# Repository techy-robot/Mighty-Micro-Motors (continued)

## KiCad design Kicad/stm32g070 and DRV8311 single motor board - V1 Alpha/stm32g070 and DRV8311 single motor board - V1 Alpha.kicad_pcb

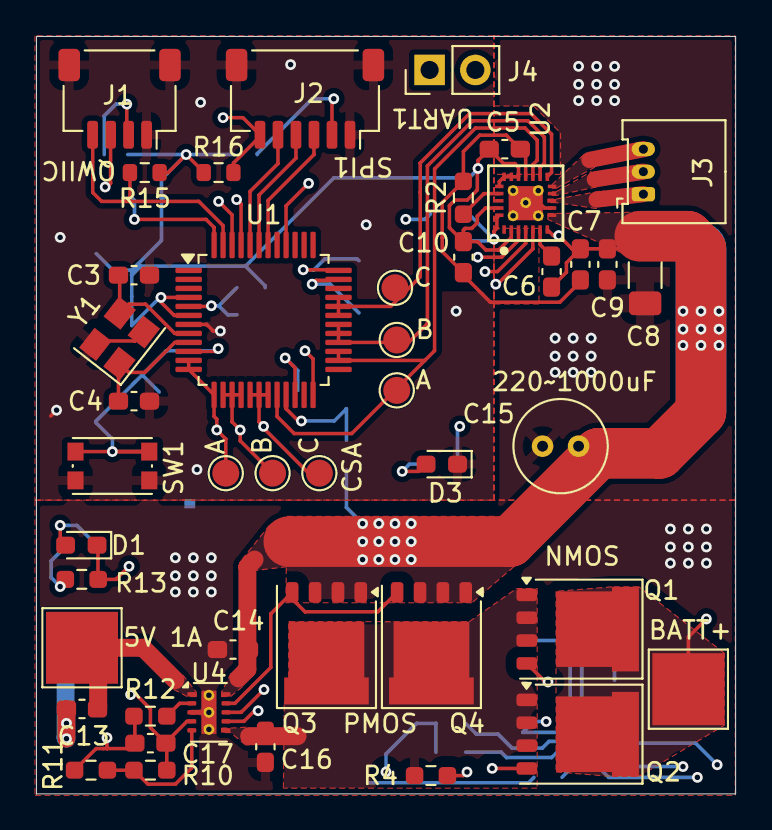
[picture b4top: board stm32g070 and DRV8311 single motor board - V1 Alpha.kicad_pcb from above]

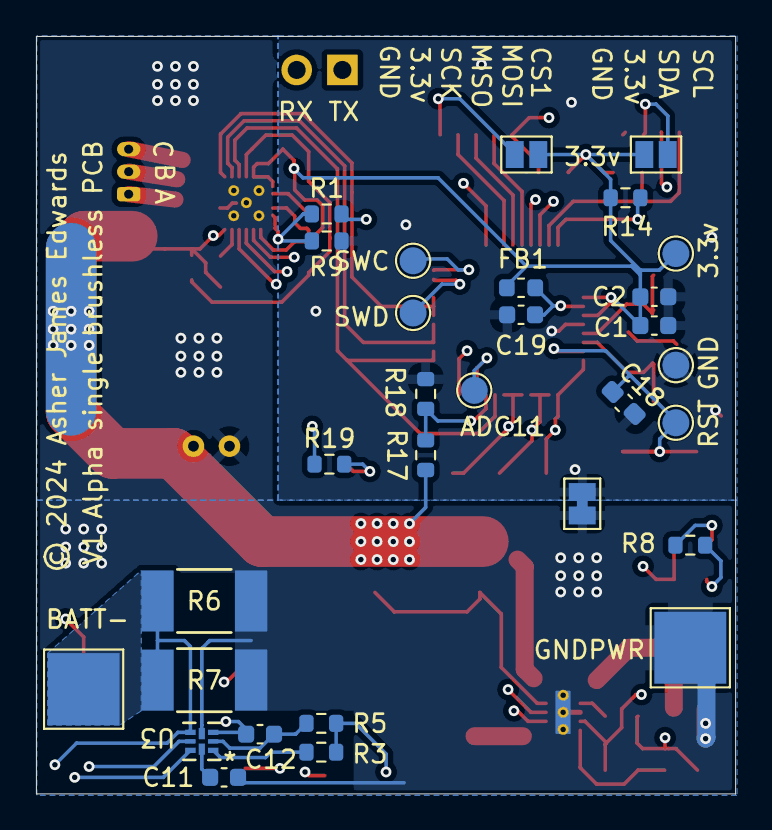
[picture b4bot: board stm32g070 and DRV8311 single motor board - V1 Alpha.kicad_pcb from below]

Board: 4 copper layers, 38.8 x 42.1 mm, 74 parts (30 on the bottom side), 51 nets.

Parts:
C1, C19: 0.1uF; C_0603_1608Metric
C2: 4.7uF; C_0603_1608Metric
C3, C4: 12pF; C_0603_1608Metric_Pad1.08x0.95mm_HandSolder
C5: 4.7uF; C_0603_1608Metric_Pad1.08x0.95mm_HandSolder
C6, C7, C9: 0.1uF, 16v; C_0603_1608Metric_Pad1.08x0.95mm_HandSolder
C8: 220uF, 16 v; C_1206_3216Metric_Pad1.33x1.80mm_HandSolder
C10, C18: 0.1uF; C_0603_1608Metric_Pad1.08x0.95mm_HandSolder
C11: 8nF; C_0603_1608Metric
C12: 1uF, 16v; C_0603_1608Metric
C13, C14, C16: 10uF, 16v; C_0603_1608Metric_Pad1.08x0.95mm_HandSolder
C15: 1000uF, 16v; C_Radial_D5.0mm_H5.0mm_P2.00mm
C17: 1uF; C_0603_1608Metric_Pad1.08x0.95mm_HandSolder
D1, D3: Osram LT Q99G.01 green led; LED_0603_1608Metric_Pad1.05x0.95mm_HandSolder
FB1: 120ohm imp @100mhz; L_0603_1608Metric
H1, H2, H3, H4: 4mm_Pad; TestPoint_Pad_4.0x4.0mm
J1: JST SH SM04B; JST_SH_SM04B-SRSS-TB_1x04-1MP_P1.00mm_Horizontal
J2: JST SH SM06B; JST_SH_SM06B-SRSS-TB_1x06-1MP_P1.00mm_Horizontal
J3: Molex_PicoBlade_53048-0310 Horizontal 3P; Molex_PicoBlade_53048-0310_1x03_P1.25mm_Horizontal
J4: Conn_01x02_Pin; PinHeader_1x02_P2.54mm_Vertical
JP1, JP2: VCC; SolderJumper-2_P1.3mm_Bridged_Pad1.0x1.5mm
L1: GND joiner; SolderJumper-2_P1.3mm_Bridged_Pad1.0x1.5mm
Q1: NMOS, sir404dp; PQFN-8-EP_6x5mm_P1.27mm_Generic
Q2: NMOS; PQFN-8-EP_6x5mm_P1.27mm_Generic
Q3: PMOS,Si7157DP; PQFN-8-EP_6x5mm_P1.27mm_Generic
Q4: PMOS; PQFN-8-EP_6x5mm_P1.27mm_Generic
R1, R17: 100k; R_0603_1608Metric
R2: 47k; R_0603_1608Metric_Pad0.98x0.95mm_HandSolder
R3: 20ohm; R_0603_1608Metric
R4, R13: 2k; R_0603_1608Metric_Pad0.98x0.95mm_HandSolder
R5: 300ohm; R_0603_1608Metric
R6: Same, 1000uOhm; RES_WSLF2512_VIS-M
R7: Vishay WSLF2512, 1%, 300uOhm; RES_WSLF2512_VIS-M
R8: 402 ohm; R_0603_1608Metric
R9, R18: 150k; R_0603_1608Metric
R10, R12: 1k; R_0603_1608Metric_Pad0.98x0.95mm_HandSolder
R11: 230ohm; R_0603_1608Metric_Pad0.98x0.95mm_HandSolder
R14, R15, R16: 10k; R_0603_1608Metric
R19: 80.6 ohm; R_0603_1608Metric
SW1: SW_Push; SW_Push_1P1T_NO_CK_KMR2
TP1, TP2, TP3, TP4, TP5, TP6: TestPoint; TestPoint_Pad_D1.5mm
TP7, TP8, TP9, TP10, TP11, TP12: TestPoint_Pad_D1.5mm
U1: STM32G070CBTr; LQFP-48_7x7mm_P0.5mm
U2: DRV8311HRRWR; DRV8311_0.3mmVias
U3: BQ298012RUGT; RUG8_TEX
U4: BQ25060; WSON-10-1EP_2x3mm_P0.5mm_EP0.84x2.4mm_ThermalVias_0.3mm
Y1: ABM8-16.000MHZ-10-1-U-T; Crystal_SMD_Abracon_ABM8G-4Pin_3.2x2.5mm

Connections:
/1A: TP7.1, U1.20 (PB1), U1.26 (PB14), U1.27 (PB15), U2.15 (INHA)
/1B: TP8.1, U1.28 (PA8), U1.29 (PA9/NC), U1.30 (PC6), U2.14 (INHB)
/1C: TP9.1, U1.31 (PC7), U1.32 (PA10/NC), U1.33 (PA11/PA9), U2.13 (INHC)
/1CSA-A: TP10.1, U1.11 (PA0), U1.12 (PA1), U1.13 (PA2), U2.5 (SOA)
/1CSA-B: TP11.1, U1.14 (PA3), U1.15 (PA4), U1.16 (PA5), U2.4 (SOB)
/1CSA-C: TP12.1, U1.17 (PA6), U1.18 (PA7), U1.19 (PB0), U2.3 (SOC)
/ADC10/VBATT: R17.1, R18.2, U1.21 (PB2)
/ADC11: TP6.1, U1.22 (PB10)
/CS1: J2.6, R16.2, U1.40 (PD2)
/LED: R19.1, U1.24 (PB12)
/MISO1: J2.4, U1.43 (PB4)
/MOSI1: J2.5, U1.44 (PB5)
/MOTORPWR: C6.2, C7.1, C8.1, C9.1, C14.1, C15.1, Q3.1 (S), Q3.2 (S), Q3.3 (S), Q4.1 (S), Q4.2 (S), Q4.3 (S), R1.2, R17.2, U2.7 (VIN_AVDD), U2.8 (VM), U4.10 (OUT)
/NRST: C18.1, SW1.2, TP1.1, U1.10 (NRST)
/PSU/BATT+: H1.1, Q1.5 (D), Q2.5 (D), R3.1, R5.1
/PSU/BATT-: C12.2, H2.1, R6.1, R7.1, U3.3 (VSS), U3.5 (CTR)
/PSU/IN: C13.1, H3.1, U4.1 (IN)
/PSU/LDO 4.9v: C17.2, R8.1, R10.1, R13.2, U4.4 (LDO)
/PSU/Pack+: C16.2, Q1.1 (S), Q1.2 (S), Q1.3 (S), Q2.1 (S), Q2.2 (S), Q2.3 (S), Q3.5 (D), Q4.5 (D), R4.1, U4.6 (BAT)
/PSU/~CHG: D1.1 (K), R13.1, U4.8 (~CHG)
/SCK1: J2.3, U1.42 (PB3)
/SCL1: J1.4, R15.2, U1.47 (PB8)
/SDA1: J1.3, R14.2, U1.48 (PB9)
/SWC: TP3.1, U1.36 (PA14)
/SWD: TP2.1, U1.35 (PA13)
/USART1_RX: J4.2, U1.46 (PB7)
/USART1_TX: J4.1, U1.45 (PB6)
GND: C1.2, C2.2, C3.2, C4.2, C5.1, C7.2, C10.1, C17.1, C18.2, C19.1, D3.1 (K), J1.1, J1.MP (MountPin), J2.1, J2.MP (MountPin), L1.1, R2.1, R9.1, R11.2, R12.1, R18.1, SW1.1, TP5.1, U1.7 (VSS), U2.16 (AGND), U4.7 (EN), Y1.2, Y1.4
GNDPWR: C8.2, C9.2, C11.2, C13.2, C14.2, C15.2, C16.1, H4.1, L1.2, R6.2, R7.2, U2.9 (PGND), U2.25 (PowerPAD), U3.4 (CS), U4.3 (VSS), U4.11 (VSS)
unnamed: D1.2 (A), R8.2
unnamed: D3.2 (A), R19.2
unnamed: J1.2, JP1.2 (B)
unnamed: J2.2, JP2.2 (B)
unnamed: J3.1, U2.10 (OUTA)
unnamed: J3.2, U2.11 (OUTB)
unnamed: J3.3, U2.12 (OUTC)
unnamed: Q1.4 (G), Q2.4 (G), U3.7 (DSG)
unnamed: Q3.4 (G), Q4.4 (G), U4.9 (BGATE)
unnamed: C3.1, U1.8 (PF0), Y1.3
unnamed: C4.1, U1.9 (PF1), Y1.1
unnamed: C19.2, FB1.1, U1.5 (VREF+)
unnamed: C6.1, U2.6 (CP)
unnamed: R2.2, U2.21 (GAIN)
unnamed: R1.1, R9.2, U2.24 (SLEEP_N)
unnamed: R3.2, U3.1 (BAT)
unnamed: C11.1, U3.8 (CHG)
unnamed: R4.2, U3.6 (PACK)
unnamed: C12.1, R5.2, U3.2 (VDD)
unnamed: R12.2, U4.2 (ISET)
unnamed: R10.2, R11.1, U4.5 (TS)
VDD: C1.1, C2.1, C5.2, C10.2, FB1.2, JP1.1 (A), JP2.1 (A), R14.1, R15.1, R16.1, TP4.1, U1.4 (VBAT), U1.6 (VDD), U2.2 (CSAREF), U2.17 (AVDD), U2.18 (INLA), U2.19 (INLB), U2.20 (INLC), U2.23 (MODE)

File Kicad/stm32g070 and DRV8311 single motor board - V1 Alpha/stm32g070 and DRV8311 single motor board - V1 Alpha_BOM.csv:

"Reference","Value","Datasheet","Footprint","Qty","DNP"
"C1,C10,C18,C19","0.1uF","~","-- mixed values --","4",""
"C2,C5","4.7uF","~","-- mixed values --","2",""
"C3,C4","12pF","~","Capacitor_SMD:C_0603_1608Metric_Pad1.08x0.95mm_HandSolder","2",""
"C6,C7,C9","0.1uF, 16v","~","Capacitor_SMD:C_0603_1608Metric_Pad1.08x0.95mm_HandSolder","3",""
"C11","8nF","~","Capacitor_SMD:C_0603_1608Metric","1",""
"C12","1uF, 16v","~","Capacitor_SMD:C_0603_1608Metric","1",""
"C13,C14,C16","10uF, 16v","~","Capacitor_SMD:C_0603_1608Metric_Pad1.08x0.95mm_HandSolder","3",""
"C15","1000uF, 16v","~","Capacitor_THT:C_Radial_D5.0mm_H5.0mm_P2.00mm","1",""
"C17","1uF","~","Capacitor_SMD:C_0603_1608Metric_Pad1.08x0.95mm_HandSolder","1",""
"D1,D3","Osram LT Q99G.01 green led","~","LED_SMD:LED_0603_1608Metric_Pad1.05x0.95mm_HandSolder","2",""
"FB1","120ohm imp @100mhz","~","Inductor_SMD:L_0603_1608Metric","1",""
"J1","JST SH SM04B","~","Connector_JST:JST_SH_SM04B-SRSS-TB_1x04-1MP_P1.00mm_Horizontal","1",""
"J2","JST SH SM06B","~","Connector_JST:JST_SH_SM06B-SRSS-TB_1x06-1MP_P1.00mm_Horizontal","1",""
"J3","Molex_PicoBlade_53048-0310 Horizontal 3P","~","Connector_Molex:Molex_PicoBlade_53048-0310_1x03_P1.25mm_Horizontal","1",""
"J4","Conn_01x02_Pin","~","Connector_PinHeader_2.54mm:PinHeader_1x02_P2.54mm_Vertical","1",""
"L1","GND joiner","~","Jumper:SolderJumper-2_P1.3mm_Bridged_Pad1.0x1.5mm","1",""
"Q1","NMOS, sir404dp","https://ngspice.sourceforge.io/docs/ngspice-html-manual/manu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","Package_DFN_QFN:PQFN-8-EP_6x5mm_P1.27mm_Generic","1",""
"Q2","NMOS","https://ngspice.sourceforge.io/docs/ngspice-html-manual/manu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","Package_DFN_QFN:PQFN-8-EP_6x5mm_P1.27mm_Generic","1",""
"Q3","PMOS,Si7157DP","https://ngspice.sourceforge.io/docs/ngspice-html-manual/manu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","Package_DFN_QFN:PQFN-8-EP_6x5mm_P1.27mm_Generic","1",""
"Q4","PMOS","https://ngspice.sourceforge.io/docs/ngspice-html-manual/manu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","Package_DFN_QFN:PQFN-8-EP_6x5mm_P1.27mm_Generic","1",""
"R1,R17","100k","~","Resistor_SMD:R_0603_1608Metric","2",""
"R2","47k","~","Resistor_SMD:R_0603_1608Metric_Pad0.98x0.95mm_HandSolder","1",""
"R3","20ohm","~","Resistor_SMD:R_0603_1608Metric","1",""
"R4,R13","2k","~","Resistor_SMD:R_0603_1608Metric_Pad0.98x0.95mm_HandSolder","2",""
"R5","300ohm","~","Resistor_SMD:R_0603_1608Metric","1",""
"R6","Same, 1000uOhm","~","vishay_wslf:RES_WSLF2512_VIS-M","1",""
"R7","Vishay WSLF2512, 1%, 300uOhm","~","vishay_wslf:RES_WSLF2512_VIS-M","1",""
"R8","402 ohm","~","Resistor_SMD:R_0603_1608Metric","1",""
"R9,R18","150k","~","Resistor_SMD:R_0603_1608Metric","2",""
"R10,R12","1k","~","Resistor_SMD:R_0603_1608Metric_Pad0.98x0.95mm_HandSolder","2",""
"R11","230ohm","~","Resistor_SMD:R_0603_1608Metric_Pad0.98x0.95mm_HandSolder","1",""
"R14,R15,R16","10k","~","Resistor_SMD:R_0603_1608Metric","3",""
"R19","80.6 ohm","~","Resistor_SMD:R_0603_1608Metric","1",""
"SW1","SW_Push","~","Button_Switch_SMD:SW_Push_1P1T_NO_CK_KMR2","1",""
"TP1,TP2,TP3,TP4,TP5,TP6","TestPoint","~","TestPoint:TestPoint_Pad_D1.5mm","6",""
"TP7,TP8,TP9,TP10,TP11,TP12","~","~","TestPoint:TestPoint_Pad_D1.5mm","6",""
"U1","STM32G070CBTr","https://www.st.com/resource/en/datasheet/stm32g070cb.pdf","Package_QFP:LQFP-48_7x7mm_P0.5mm","1",""
"U2","DRV8311HRRWR","https://www.ti.com/lit/ds/symlink/drv8311.pdf","custom_Driver_Motor:DRV8311_0.3mmVias","1",""
"U3","BQ298012RUGT","BQ298000RUGT","bq298rugt:RUG8_TEX","1",""
"U4","BQ25060","https://www.ti.com/lit/ds/symlink/bq25060.pdf","custom_Power:WSON-10-1EP_2x3mm_P0.5mm_EP0.84x2.4mm_ThermalVias_0.3mm","1",""
"Y1","ABM8-16.000MHZ-10-1-U-T","~","Crystal:Crystal_SMD_Abracon_ABM8G-4Pin_3.2x2.5mm","1",""

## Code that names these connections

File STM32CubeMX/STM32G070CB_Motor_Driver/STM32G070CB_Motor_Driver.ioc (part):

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Mcu.Name=STM32G070CBTx
Mcu.Package=LQFP48
Mcu.UserName=STM32G070CBTx
PA0.Mode=IN0
PA0.Signal=ADC1_IN0
PA1.Mode=IN1
PA1.Signal=ADC1_IN1
PA10.Signal=S_TIM1_CH3
PA11\ [PA9].Signal=S_TIM1_CH4
PA12\ [PA10].Mode=I2C
PA12\ [PA10].Signal=I2C2_SDA
PA13.Mode=Serial_Wire
PA13.Signal=SYS_SWDIO
PA14-BOOT0.Mode=Serial_Wire
PA14-BOOT0.Signal=SYS_SWCLK
PA2.Mode=IN2
PA2.Signal=ADC1_IN2
PA3.Mode=IN3
PA3.Signal=ADC1_IN3
PA4.Mode=IN4
PA4.Signal=ADC1_IN4
PA5.Mode=IN5
PA5.Signal=ADC1_IN5
PA6.Mode=IN6
PA6.Signal=ADC1_IN6
PA7.Mode=IN7
PA7.Signal=ADC1_IN7
PA8.Signal=S_TIM1_CH1
PA9.Signal=S_TIM1_CH2
PB0.Mode=IN8
PB0.Signal=ADC1_IN8
PB1.Signal=S_TIM3_CH4
PB10.Mode=IN11
PB10.Signal=ADC1_IN11
PB11.Mode=Full_Duplex_Master
PB11.Signal=SPI2_MOSI
PB13.Mode=I2C
PB13.Signal=I2C2_SCL
PB14.Signal=S_TIM15_CH1
PB15.Signal=S_TIM15_CH2
PB2.Mode=IN10
PB2.Signal=ADC1_IN10
PB3.Mode=Full_Duplex_Master
PB3.Signal=SPI1_SCK
PB4.Mode=Full_Duplex_Master
PB4.Signal=SPI1_MISO
PB5.Mode=Full_Duplex_Master
PB5.Signal=SPI1_MOSI
PB6.Mode=Asynchronous
PB6.Signal=USART1_TX
PB7.Mode=Asynchronous
PB7.Signal=USART1_RX
PB8.Mode=I2C
PB8.Signal=I2C1_SCL
PB9.Mode=I2C
PB9.Signal=I2C1_SDA
PC6.Signal=S_TIM3_CH1
PC7.Signal=S_TIM3_CH2
PD1.Mode=Full_Duplex_Master
PD1.Signal=SPI2_SCK
PD3.Mode=Full_Duplex_Master
PD3.Signal=SPI2_MISO
PF0-OSC_IN\ (PF0).Mode=HSE-External-Oscillator
PF0-OSC_IN\ (PF0).Signal=RCC_OSC_IN
PF1-OSC_OUT\ (PF1).Mode=HSE-External-Oscillator
PF1-OSC_OUT\ (PF1).Signal=RCC_OSC_OUT
RCC.HSE_VALUE=16000000
RCC.SYSCLKFreq_VALUE=64000000
RCC.SYSCLKSource=RCC_SYSCLKSOURCE_PLLCLK
board=custom

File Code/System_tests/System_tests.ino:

/*
  Created by Asher Edwards
  Last updated Jul 16, 2024
*/

#include <hal_conf_extra.h> 
#include <SPI.h>

// Clock settings, the only thing changed from default was the clock source for external
extern "C" void SystemClock_Config(void)
{
  RCC_OscInitTypeDef RCC_OscInitStruct = {};
  RCC_ClkInitTypeDef RCC_ClkInitStruct = {};

  /** Configure the main internal regulator output voltage
  */
  HAL_PWREx_ControlVoltageScaling(PWR_REGULATOR_VOLTAGE_SCALE1);
  /** Initializes the RCC Oscillators according to the specified parameters
  * in the RCC_OscInitTypeDef structure. Here I have enabled the external clcok as the source
  */
  RCC_OscInitStruct.OscillatorType = RCC_OSCILLATORTYPE_HSE;
  RCC_OscInitStruct.HSEState = RCC_HSE_ON;
  RCC_OscInitStruct.PLL.PLLState = RCC_PLL_ON;
  RCC_OscInitStruct.PLL.PLLSource = RCC_PLLSOURCE_HSE;
  RCC_OscInitStruct.PLL.PLLM = RCC_PLLM_DIV1;
  RCC_OscInitStruct.PLL.PLLN = 8;
  RCC_OscInitStruct.PLL.PLLP = RCC_PLLP_DIV2;
  RCC_OscInitStruct.PLL.PLLR = RCC_PLLR_DIV2;
  if (HAL_RCC_OscConfig(&RCC_OscInitStruct) != HAL_OK) {
    Error_Handler();
  }
  /** Initializes the CPU, AHB and APB buses clocks
  */
  RCC_ClkInitStruct.ClockType = RCC_CLOCKTYPE_HCLK | RCC_CLOCKTYPE_SYSCLK
                                | RCC_CLOCKTYPE_PCLK1;
  RCC_ClkInitStruct.SYSCLKSource = RCC_SYSCLKSOURCE_PLLCLK;
  RCC_ClkInitStruct.AHBCLKDivider = RCC_SYSCLK_DIV1;
  RCC_ClkInitStruct.APB1CLKDivider = RCC_HCLK_DIV1;

  if (HAL_RCC_ClockConfig(&RCC_ClkInitStruct, FLASH_LATENCY_2) != HAL_OK) {
    Error_Handler();
  }
}

//-----------------Pins-------------------

#define LED PB12

#define CSA_A PA0 //PA0 - 2
#define CSA_B PA3 //PA3 - 5
#define CSA_C PA6 //PA6,PA7,PB0

#define OUT_A PB1 //PB1, PB14, PB14
#define OUT_B PA8 //PA8, PA9, PC6
#define OUT_C PA6 //PC7, PA10, PA11

#define CS1 PD2 //for the first SPI bus

//Found in the datasheet. This is in mV
#define VREFINT 1212
#define ADC_RANGE 4096

//-------------------Interfaces-------------------------
//                      RX    TX
HardwareSerial Serial1(PB7, PB6);

//         MOSI  MISO  SCLK  SSEL
SPIClass SPI_1(PB5, PB4, PB3);

const byte READ = 0b01000000;     // MA735 read command
const byte WRITE = 0b10000000;   // MA735's write command

// the setup function runs once when you press reset or power the board
void setup() {
  // initialize digital pin PB12 as an output. This is the LED pin on my stm32 based motor control board
  pinMode(LED, OUTPUT);

  pinMode(CS1, OUTPUT);
  SPI_1.begin();

  pinMode(CSA_A, INPUT);
  pinMode(CSA_B, INPUT);
  pinMode(CSA_C, INPUT);
  analogReadResolution(12);//Max value is 4096, at 3.3v

  Serial1.begin(19200);

  //Blink twice on start
  digitalWrite(LED, HIGH);
  delay(200);
  digitalWrite(LED, LOW);
  delay(200);
  digitalWrite(LED, HIGH);
  delay(200);
  digitalWrite(LED, LOW);
}

// the loop function runs over and over again forever
void loop() {

  int a = analogRead(CSA_A);
  int b = analogRead(CSA_B);
  int c = analogRead(CSA_C);
  float vref = readVref();

  Serial1.print("Clock freq is: ");//check system clock speed
  Serial1.println(F_CPU);
  Serial1.print("CSA Voltages: ");
  Serial1.print(String(readVoltage(vref, CSA_A)) + ", ");
  Serial1.print(String(readVoltage(vref, CSA_B)) + ", ");
  Serial1.println(String(readVoltage(vref, CSA_C)));
  Serial1.println("Vref(mV):" + String(vref));
  Serial1.println("Vbat(V):" + String(readVoltage(vref, AVBAT)));
  Serial1.println("Temperature(°C):" + String(readTempSensor(vref)));
  Serial1.println("Sensor Data: " + String(readSensor()));
  delay(2000);
}

//alternative analog to voltage, but accounting for voltage reference
static float readVoltage(int32_t VRef, uint32_t pin) {
  return (__LL_ADC_CALC_DATA_TO_VOLTAGE(VRef, analogRead(pin), LL_ADC_RESOLUTION_12B))/1000.0;
}


static int32_t readVref() {
  return (VREFINT * ADC_RANGE / analogRead(AVREF)); // ADC sample to mV
}

static int32_t readTempSensor(int32_t VRef) {
  return (__LL_ADC_CALC_TEMPERATURE(VRef, analogRead(ATEMP), LL_ADC_RESOLUTION_12B));
}

//Read the sensor data
unsigned int readSensor() {
  byte inByte = 0;           // incoming byte from the SPI
  unsigned int result = 0;   // result to return

  // take the chip select low to select the device:
  digitalWrite(CS1, LOW);
  // send a value of 0 to read the bytes
  result = SPI_1.transfer(0x00);//first part
  result = result << 8;
  inByte = SPI_1.transfer(0x00);//second part
  // combine the byte you just got with the previous one:
  result = result | inByte;
  // take the chip select high to de-select:
  digitalWrite(CS1, HIGH);
  // return the result:
  return (result);
}

//Read from a register:
unsigned int readRegister(byte thisRegister, int bytesToRead) {
  byte inByte = 0;           // incoming byte from the SPI
  unsigned int result = 0;   // result to return
  Serial.print(thisRegister, BIN);
  Serial.print("\t");
  // MA735 expects the register name to be in the lower 5 bits
  // of the byte. So shift the bits right by three bits:
  thisRegister = thisRegister >> 3;
  // now combine the address and the command into one byte
  uint16_t dataToSend = READ & thisRegister ; //Read should be 010 in binary
  Serial.println(thisRegister, BIN);
  // take the chip select low to select the device:
  digitalWrite(CS1, LOW);
  // send the device the register you want to read:
  SPI_1.transfer(dataToSend);
  // send a value of 0 to read the first byte returned:
  result = SPI_1.transfer(0x00);
  // decrement the number of bytes left to read:
  bytesToRead--;
  // if you still have another byte to read:
  if (bytesToRead > 0) {
    // shift the first byte left, then get the second byte:
    result = result << 8;
    inByte = SPI_1.transfer(0x00);
    // combine the byte you just got with the previous one:
    result = result | inByte;
    // decrement the number of bytes left to read:
    bytesToRead--;
  }
  // take the chip select high to de-select:
  digitalWrite(CS1, HIGH);
  // return the result:
  return (result);
}

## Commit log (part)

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2024-06-26 Adding current Kicad files
    I previously was not tracking these files on GitHub, so its a rather big commit.
2024-07-05 Filled out README documentation
    Added a description of the project and the individual components.
2024-07-05 Added Progress Log with pictures
2024-07-06 Created Blink example sketch and changed pin number
2024-07-07 Updated progress log, Added Flipper zero programmer support
    Make sure to delete `.config/arduino-ide` to clear up the cache and get the programmer to show up.
2024-07-07 Added correct path for openocd runtime
    In the definition when you have .path, it actually means go one more folder down. That way you don't have to manually type the version number.
2024-07-07 Add pulsing LED heartbeat instead to try out
2024-07-08 Trying out clock settings and serial support
2024-07-16 Fixed Analog read encoding error
2024-07-16 Added internal analog read for temp and for input voltage
2024-07-16 Updated CSA analog reads to use VREF
2024-07-16 Working SPI sensor data read
    The issue was with the default pin definitions. I created an instance with the correct SPI pins.
2024-07-16 Started writing SimpleFOC setup code
2024-07-17 Preliminary MA735 support
    All I did in this was copy the MA730 code and rename everything.
2024-07-17 Added missing registers and cmds
    The two that weren't already implemented was the resolution/speed tradeoff setting (Filter Window), and the ABZ hysteresis setting.
2024-07-17 Fixed switch case typos
    It wasn't compiling last night, because of a few typos. Also switch statements only operate on integers or similar, not strings or floats.
2024-07-17 Added write safety check
    It reads the register before writing. If it is the exact same value, it will not write. This saves time and increases the NVM lifetime, since it has only 1000 cycles!
2024-07-17 Added motor phase resistance, update Log
2024-07-17 Update progress log, compiled code
    I had the wrong names for commander in some places. Code takes up 80kb!
2024-07-18 Some quick fixes
    The motors will spin, however it is only at 100 radians/s and it doesn't like other speeds higher or lower. It whines a lot.
2024-07-18 Back to sinusoidal, changed current sense amount
2024-07-19 Magnetic encoder motor test piece complete
2024-07-19 Skip current sense alignment
    It worked on initialization, however it keeps swapping to the wrong pins. All the current sense align really does is checks and fixes pin errors, but I am pretty sure the pins match up
2024-07-23 Added timing mechanism, absolute sensor position
    I also switched to SpaceVectorPWM because its more efficient, and bumped the current limit back up to 2.5 amps
2024-07-23 Added update time command, and serial usb wait
2024-07-25 Start rework of gearbox base
    I am adding parametric variables in Onshape, and added screw holes that should universally support all my future gearboxes
2024-07-25 Added fan blade on central shaft
    This is a paddle blade like found in power tools and drills. Its not a very efficient fan blade but it works in both directions. Onshape: https://cad.onshape.com/documents/c861ec30af8169cf9c14bd7f/w/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
2024-07-26 Incomplete cycloidal with pass through
    Onshape: https://cad.onshape.com/documents/c861ec30af8169cf9c14bd7f/w/e538486c85e6a5fe77cd1d33/m/884b7a8ee5dcba20016fd244/e/7383c3da91d908f3c2a75881
2024-07-27 Added wire slots in cycloidal
    Onshape: https://cad.onshape.com/documents/c861ec30af8169cf9c14bd7f/w/e538486c85e6a5fe77cd1d33/m/a67cb1fcdf15daad4af4e84a/e/7383c3da91d908f3c2a75881
2024-07-27 Shrinking disc size
    Currently it looks like the smallest I can feasible go is 16mm. I have the number of teeth set to be divisible by 3, so the 3 axle bearings can nestle into the patter of the teeth. I also started wor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
    Onshape: https://cad.onshape.com/documents/c861ec30af8169cf9c14bd7f/w/e538486c85e6a5fe77cd1d33/m/ab9855c3639a3ccbf2450367/e/7383c3da91d908f3c2a75881
2024-07-28 Can't figure out eccentric screw and wire holes
    Onshape: https://cad.onshape.com/documents/c861ec30af8169cf9c14bd7f/w/e538486c85e6a5fe77cd1d33/m/1e100a53234ceef647306cbe/e/7383c3da91d908f3c2a75881
2024-07-29 Tolerance adjustments and adding bearing
    I tweaked a lot of the tolerances, and added bearings around all the little rods.
    Onshape: https://cad.onshape.com/documents/c861ec30af8169cf9c14bd7f/w/e538486c85e6a5fe77cd1d33/m/66f398e2432e977fad1e9c49/e/395711bbc38dcc987be1be1a
2024-07-29 Fixed 2nd disc, working on output stage
    Onshape: https://cad.onshape.com/documents/c861ec30af8169cf9c14bd7f/w/e538486c85e6a5fe77cd1d33/m/98de684524afdfbcdc4f0564/e/7383c3da91d908f3c2a75881
2024-07-29 Finished sensor mount
    Unfortunately the magnet needed for encoding is sticking out the top quite a bit. The only way I could fix this is if I remove the sensor from the on axis position and moved it to the side, which wou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
    Onshape: https://cad.onshape.com/documents/c861ec30af8169cf9c14bd7f/w/e538486c85e6a5fe77cd1d33/m/034e83fa55fcec580c0735db/e/7383c3da91d908f3c2a75881
2024-07-29 Still fixing broken references
    Onshape https://cad.onshape.com/documents/c861ec30af8169cf9c14bd7f/w/e538486c85e6a5fe77cd1d33/m/b95fba314a62f127e0e52bbb/e/7383c3da91d908f3c2a75881
2024-07-30 Animated cycloidal
    Note that the changes are only visible in Onshape really
    Onshape: https://cad.onshape.com/documents/c861ec30af8169cf9c14bd7f/w/e538486c85e6a5fe77cd1d33/m/0fd09e6c676fce52f4df5401/e/395711bbc38dcc987be1be1a
2024-07-31 Added STL files and Lychee slicer profile, tweaked dimensions after failed
    I got a terrible print, with a ton of flakes and a lot of snapped stuff. All the big parts failed too. Of the parts that didn't fail, I was able to test fit, so I tweaked some dimensions.
2024-08-04 Updated progress log & README
    I have been slacking the last 2 weeks on giving progress updates (besides commits), so I have updated the log with pictures and what I've been up to. Also updated the main README.
2024-08-05 WIP pinout utilization
    I have most of the important pins worked, still need to figure out my communication interfaces
2024-08-06 Adding ESP32-S3 code
    Note that the board support requires python3-pyserial system package to run.
2024-08-07 Update gearbox base
2024-08-07 Partial layout complete
    I currently have the board sized at 4.5mm with a really long cable. This is probably WAY to small, I can barely fit the 0402 capacitors.
2024-08-10 Rename LICENSE to LICENSE.readme
2024-08-10 Finished 7pin fpc contacts
2024-08-10 Changed everything to 0.2mm traces and 0.3mm vias for cost
    Its a tight fit but everything works out okay. Note that the trace minimum gap is half of the typical, its at 0.1mm. Most board manufactures should be able to handle this, but it may still add an add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
2024-08-13 Fixed longstanding silkscreen bug
    Mosi and Miso were swapped
2024-08-13 Mostly finished draft wiring
    I added test points to practically every pin I won't be using regularly. Even if I never use a pin, it is better to have it exposed somehow than to try to solder to a tiny pitch pad
2024-08-14 Wired decoupling capacitors and crystal
2024-08-15 Wire mess progress
2024-08-16 Finished routing everything
2024-08-17 Fixed Silkscreen
2024-08-17 Started migrating driver to the back of the motor
    If successful, this will save a ton of space. This will be a mess for awhile.
2024-08-18 Finished component layout
    The current board diameter is 12mm, though I may be able to shrink it down to 10mm. Its already REALLY small, with those 0402 components. It would be nice if the board didn't exceed the outer diamete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
2024-08-18 Finished routing, distribute pwr planes, silkscreen and DRC check
    The power planes were not making good connection previously, so I have fixed that.
    Silkscreen is done, the last traces have been routed, and there isn't much I can do
    As far as I'm concerned, this board is done!
2024-08-18 Removed drv8311 section on the main board
    Don't need it now that I have it off-board.
2024-08-21 Starting work on replacing battery charger with 2s version
    The charger module will be way too big, but I really think I need this. Hopefully I can find a more integrated charger
2024-08-23 Finished basic balance charge circuit
    Passive values still need to be tweaked, and the datasheet needs to be checked again.
2024-08-23 Added footprints and started layout
2024-08-24 Reached target dimensions of 15x45mm
    I imagine heat will be crazy, but hey, its small!
2024-08-24 Re-arranging some components, continue routing
2024-08-24 Wiring complete except for i2c
    This is the trickiest to wire.
2024-08-24 Finished PCB with 2s battery charger
    Silkscreen is all finished
2024-08-24 Adding usage notes and required pullup resistors
2024-08-25 Replacing sense resistors, started routing additional pullup resistors
2024-08-25 Silkscreen and smd clearance cleanup
    Everything was complete, but I identified a new issue on the board to fix soon. I will have to switch the battery balance chip to the other side of the board to be closer to the current sense resisto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
2024-08-25 Fixing routing issues after change
2024-08-25 Updated README with current progress and V2 pcb
2024-08-26 Added sensor flex cable routing and reduced vertical space
    The top is now flush, since I have chosen a different magnet.
    I also added some support towers back in, including a new one for the sensor flex cable.
    Onshape: https://cad.onshape.com/documents/c861ec30af8169cf9c14bd7f/w/e538486c85e6a5fe77cd1d33/m/7b5e3d6ef87d963f5ec9f7a0/e/7383c3da91d908f3c2a75881
2024-08-27 Fixing magnet top and flex cable path
    Onshape: https://cad.onshape.com/documents/c861ec30af8169cf9c14bd7f/w/e538486c85e6a5fe77cd1d33/m/3281a3f827947617db59824e/e/7383c3da91d908f3c2a75881
2024-08-27 Added wire cutouts and bottom pcb mount
    Onshape: https://cad.onshape.com/documents/c861ec30af8169cf9c14bd7f/w/e538486c85e6a5fe77cd1d33/m/7004cd96ee038b80e9d115f4/e/395711bbc38dcc987be1be1a
2024-08-27 Changing outer ring to the output shaft
    Onshape: https://cad.onshape.com/documents/c861ec30af8169cf9c14bd7f/w/e538486c85e6a5fe77cd1d33/m/85d932698391b6a8514d2cf4/e/5977e6c908e613b6ed6ca172
2024-08-28 Added planetary assembly, changed gear ratio
    Sun gear is 7 tooth, planet is 16, outer is 40.
    Onshape: https://cad.onshape.com/documents/c861ec30af8169cf9c14bd7f/w/e538486c85e6a5fe77cd1d33/m/986375f3b69578af2ff14cd6/e/cf472c2ddea246361f7a8bb4
2024-08-30 Working on adding proper gears and spacing
    Its not complete yet, but I've found two formulas on gear ratio calculation and proper spacing for this type of gearing: Onshape:https://cad.onshape.com/documents/c861ec30af8169cf9c14bd7f/w/e538486c8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
2024-08-31 Fixed gear ratios for 3 planets
    I forgot the sun and the ring for BOTH stages has to be divisible by 3. I fixed that now. Total output ratio is now 74.66:1.
    Onshape: https://cad.onshape.com/documents/c861ec30af8169cf9c14bd7f/w/e538486c85e6a5fe77cd1d33/m/03cf66b45418e8ea5545b44a/e/c076bfebf996b33c466ae250
2024-08-31 Finished assembly of gearbox
    I also had to add a gear carrier because onshape needs something that to get realistic gear motion. I haven't finished adding the gear relationships.
    Onshape: https://cad.onshape.com/documents/c861ec30af8169cf9c14bd7f/w/e538486c85e6a5fe77cd1d33/m/06649b39967f5e540a56afb8/e/c076bfebf996b33c466ae250
2024-09-15 Added sponsorship section
